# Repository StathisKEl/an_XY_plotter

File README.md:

An XY plotter that places an array of a Hall sensor and a strong magnet connected to two pieces of soft iron over specific points on a metal sheet and measures the changes in magnetic induction as the above array is moved from one point to another. From the measurements stored on an SD card, as well as the points of interest stored on the same SD card, useful conclusions can be drawn about the condition of the metal sheet.

The code inside the code_XY_plotter.ino file is under the GNU General Public v3.0 license and the hardware of the XY plotter such as the eagle pcb files and the eagle library files is under the CERN Open Hardware Version 2 - Strongly Reciprocal license. Also all the files of the 3D parts are under the Creative Commons Attribution Share Alike 4.0 International license. All the informations about the GNU General Public v3.0 license can be found in the GNU GPLv3 license.txt file, all the informations about the CERN Open Hardware Version 2 - Strongly Reciprocal license can be found in the CERN OHL S 2.0 license.txt file and all the informations about the Creative Commons Attribution Share Alike 4.0 International license can be found in the CC-BY-SA-4.0 license.txt file.

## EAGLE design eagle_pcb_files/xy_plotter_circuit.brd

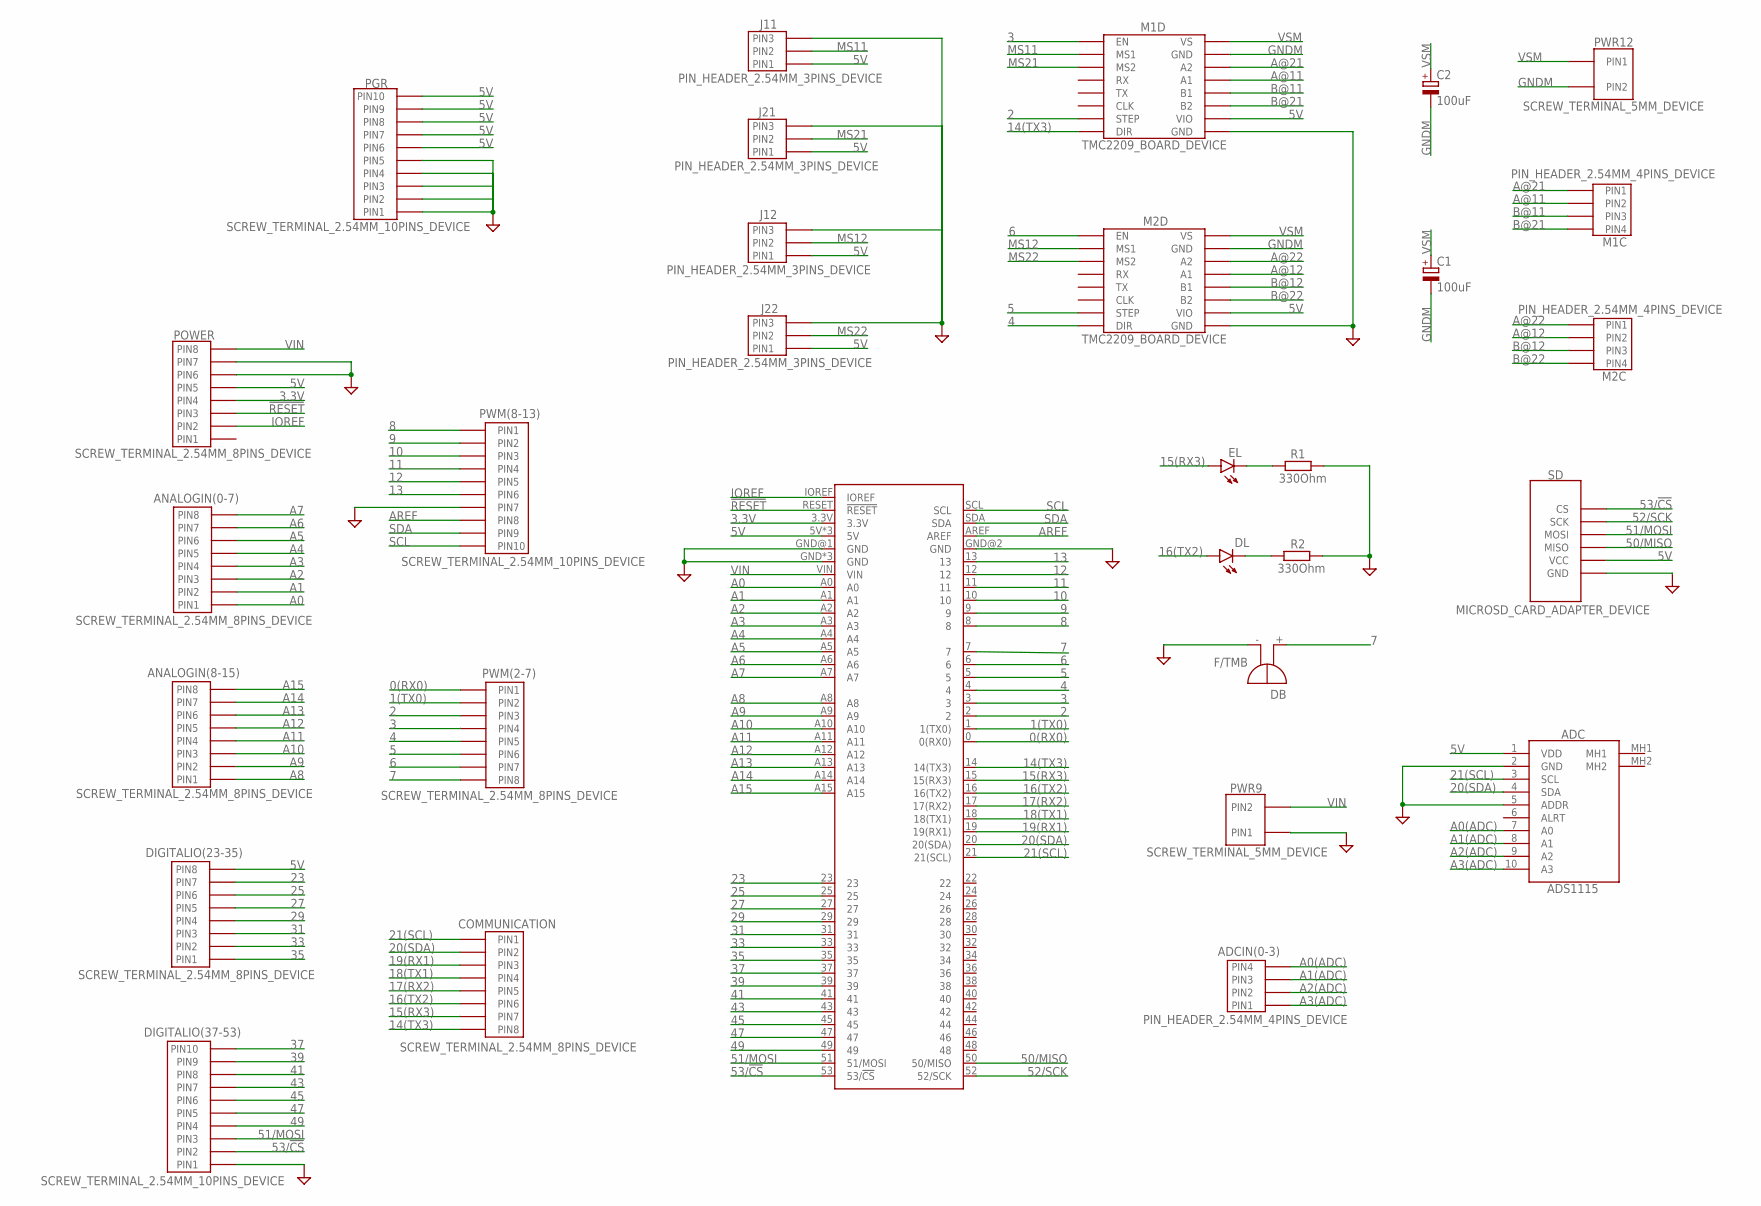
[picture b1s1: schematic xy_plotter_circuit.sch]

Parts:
ADC: ADS1115
ADCIN(0-3): PIN_HEADER_2.54MM_4PINS_DEVICE; PIN_HEADER_2.54MM_4PINS_FOOTPRINT
ANALOGIN(0-7), ANALOGIN(8-15): SCREW_TERMINAL_2.54MM_8PINS_DEVICE; SCREW_TERMINAL_2.54MM_8PINS_FOOTPRINT
ARDUINO: ARDUINO_MEGA_R3FULL; ARDUINO_MEGA_NO_SILK
C1, C2: 100uF; E2,5-7
COMMUNICATION: SCREW_TERMINAL_2.54MM_8PINS_DEVICE; SCREW_TERMINAL_2.54MM_8PINS_FOOTPRINT
DB: F/TMB
DIGITALIO(23-35): SCREW_TERMINAL_2.54MM_8PINS_DEVICE; SCREW_TERMINAL_2.54MM_8PINS_FOOTPRINT
DIGITALIO(37-53): SCREW_TERMINAL_2.54MM_10PINS_DEVICE; SCREW_TERMINAL_2.54MM_10PINS_FOOTPRINT
DL: LED3MM
EL: LED3MM
J11, J12, J21, J22: PIN_HEADER_2.54MM_3PINS_DEVICE; PIN_HEADER_2.54MM_3PINS_FOOTPRINT
M1C, M2C: PIN_HEADER_2.54MM_4PINS_DEVICE; PIN_HEADER_2.54MM_4PINS_FOOTPRINT
M1D, M2D: TMC2209_BOARD_DEVICE; TMC2209_BOARD_FOOTPRINT
PGR: SCREW_TERMINAL_2.54MM_10PINS_DEVICE; SCREW_TERMINAL_2.54MM_10PINS_FOOTPRINT
POWER: SCREW_TERMINAL_2.54MM_8PINS_DEVICE; SCREW_TERMINAL_2.54MM_8PINS_FOOTPRINT
PWM(2-7): SCREW_TERMINAL_2.54MM_8PINS_DEVICE; SCREW_TERMINAL_2.54MM_8PINS_FOOTPRINT
PWM(8-13): SCREW_TERMINAL_2.54MM_10PINS_DEVICE; SCREW_TERMINAL_2.54MM_10PINS_FOOTPRINT
PWR9, PWR12: SCREW_TERMINAL_5MM_DEVICE; SCREW_TERMINAL_5MM_FOOTPRINT
R1, R2: 330Ohm; 0207/7
SD: MICROSD_CARD_ADAPTER_DEVICE; MICROSD_CARD_ADAPTER_FOOTPRINT

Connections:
0(RX0): ARDUINO.0 (0(RX0)), PWM(2-7).PIN1
1(TX0): ARDUINO.1 (1(TX0)), PWM(2-7).PIN2
2: ARDUINO.2, M1D.STEP, PWM(2-7).PIN3
3: ARDUINO.3, M1D.EN, PWM(2-7).PIN4
3.3V: ARDUINO.3.3V, POWER.PIN4
4: ARDUINO.4, M2D.DIR, PWM(2-7).PIN5
5: ARDUINO.5, M2D.STEP, PWM(2-7).PIN6
5V: ADC.1 (VDD), ARDUINO.5V, ARDUINO.5V@1 (5V), ARDUINO.5V@2 (5V), DIGITALIO(23-35).PIN8, J11.PIN1, J12.PIN1, J21.PIN1, J22.PIN1, M1D.VIO, M2D.VIO, PGR.PIN6, PGR.PIN7, PGR.PIN8, PGR.PIN9, PGR.PIN10, POWER.PIN5, SD.VCC
6: ARDUINO.6, M2D.EN, PWM(2-7).PIN7
7: ARDUINO.7, DB.+, PWM(2-7).PIN8
8: ARDUINO.8, PWM(8-13).PIN1
9: ARDUINO.9, PWM(8-13).PIN2
10: ARDUINO.10, PWM(8-13).PIN3
11: ARDUINO.11, PWM(8-13).PIN4
12: ARDUINO.12, PWM(8-13).PIN5
13: ARDUINO.13, PWM(8-13).PIN6
14(TX3): ARDUINO.14 (14(TX3)), COMMUNICATION.PIN8, M1D.DIR
15(RX3): ARDUINO.15 (15(RX3)), COMMUNICATION.PIN7, EL.A
16(TX2): ARDUINO.16 (16(TX2)), COMMUNICATION.PIN6, DL.A
17(RX2): ARDUINO.17 (17(RX2)), COMMUNICATION.PIN5
18(TX1): ARDUINO.18 (18(TX1)), COMMUNICATION.PIN4
19(RX1): ARDUINO.19 (19(RX1)), COMMUNICATION.PIN3
20(SDA): ADC.4 (SDA), ARDUINO.20 (20(SDA)), COMMUNICATION.PIN2
21(SCL): ADC.3 (SCL), ARDUINO.21 (21(SCL)), COMMUNICATION.PIN1
23: ARDUINO.23, DIGITALIO(23-35).PIN7
25: ARDUINO.25, DIGITALIO(23-35).PIN6
27: ARDUINO.27, DIGITALIO(23-35).PIN5
29: ARDUINO.29, DIGITALIO(23-35).PIN4
31: ARDUINO.31, DIGITALIO(23-35).PIN3
33: ARDUINO.33, DIGITALIO(23-35).PIN2
35: ARDUINO.35, DIGITALIO(23-35).PIN1
37: ARDUINO.37, DIGITALIO(37-53).PIN10
39: ARDUINO.39, DIGITALIO(37-53).PIN9
41: ARDUINO.41, DIGITALIO(37-53).PIN8
43: ARDUINO.43, DIGITALIO(37-53).PIN7
45: ARDUINO.45, DIGITALIO(37-53).PIN6
47: ARDUINO.47, DIGITALIO(37-53).PIN5
49: ARDUINO.49, DIGITALIO(37-53).PIN4
50/MISO: ARDUINO.50 (50/MISO), SD.MISO
51/MOSI: ARDUINO.51 (51/MOSI), DIGITALIO(37-53).PIN3, SD.MOSI
52/SCK: ARDUINO.52 (52/SCK), SD.SCK
53/!CS: ARDUINO.53 (53/!CS), DIGITALIO(37-53).PIN2, SD.CS
!RESET: ARDUINO.RESET (!RESET), POWER.PIN3
A0: ANALOGIN(0-7).PIN1, ARDUINO.A0
A0(ADC): ADC.7 (A0), ADCIN(0-3).PIN4
A1: ANALOGIN(0-7).PIN2, ARDUINO.A1
A1(ADC): ADC.8 (A1), ADCIN(0-3).PIN3
A2: ANALOGIN(0-7).PIN3, ARDUINO.A2
A2(ADC): ADC.9 (A2), ADCIN(0-3).PIN2
A3: ANALOGIN(0-7).PIN4, ARDUINO.A3
A3(ADC): ADC.10 (A3), ADCIN(0-3).PIN1
A4: ANALOGIN(0-7).PIN5, ARDUINO.A4
A5: ANALOGIN(0-7).PIN6, ARDUINO.A5
A6: ANALOGIN(0-7).PIN7, ARDUINO.A6
A7: ANALOGIN(0-7).PIN8, ARDUINO.A7
A8: ANALOGIN(8-15).PIN1, ARDUINO.A8
A9: ANALOGIN(8-15).PIN2, ARDUINO.A9
A10: ANALOGIN(8-15).PIN3, ARDUINO.A10
A11: ANALOGIN(8-15).PIN4, ARDUINO.A11
A12: ANALOGIN(8-15).PIN5, ARDUINO.A12
A13: ANALOGIN(8-15).PIN6, ARDUINO.A13
A14: ANALOGIN(8-15).PIN7, ARDUINO.A14
A15: ANALOGIN(8-15).PIN8, ARDUINO.A15
A@11: M1C.PIN2, M1D.A1
A@12: M2C.PIN2, M2D.A1
A@21: M1C.PIN1, M1D.A2
A@22: M2C.PIN1, M2D.A2
AREF: ARDUINO.AREF, PWM(8-13).PIN8
B@11: M1C.PIN3, M1D.B1
B@12: M2C.PIN3, M2D.B1
B@21: M1C.PIN4, M1D.B2
B@22: M2C.PIN4, M2D.B2
GND: ADC.2 (GND), ADC.5 (ADDR), ARDUINO.GND, ARDUINO.GND@1 (GND), ARDUINO.GND@2 (GND), ARDUINO.GND@3 (GND), ARDUINO.GND@4 (GND), DB.-, DIGITALIO(37-53).PIN1, J11.PIN3, J12.PIN3, J21.PIN3, J22.PIN3, M1D.GND@2 (GND), M2D.GND@2 (GND), PGR.PIN1, PGR.PIN2, PGR.PIN3, PGR.PIN4, PGR.PIN5, POWER.PIN6, POWER.PIN7, PWM(8-13).PIN7, PWR9.PIN1, R1.2, R2.2, SD.GND
GNDM: C1.-, C2.-, M1D.GND@1 (GND), M2D.GND@1 (GND), PWR12.PIN2
IOREF: ARDUINO.IOREF, POWER.PIN2
MS11: J11.PIN2, M1D.MS1
MS12: J12.PIN2, M2D.MS1
MS21: J21.PIN2, M1D.MS2
MS22: J22.PIN2, M2D.MS2
unnamed: EL.K (C), R1.1
unnamed: DL.K (C), R2.1
SCL: ARDUINO.SCL, PWM(8-13).PIN10
SDA: ARDUINO.SDA, PWM(8-13).PIN9
VIN: ARDUINO.VIN, POWER.PIN8, PWR9.PIN2
VSM: C1.+, C2.+, M1D.VS, M2D.VS, PWR12.PIN1

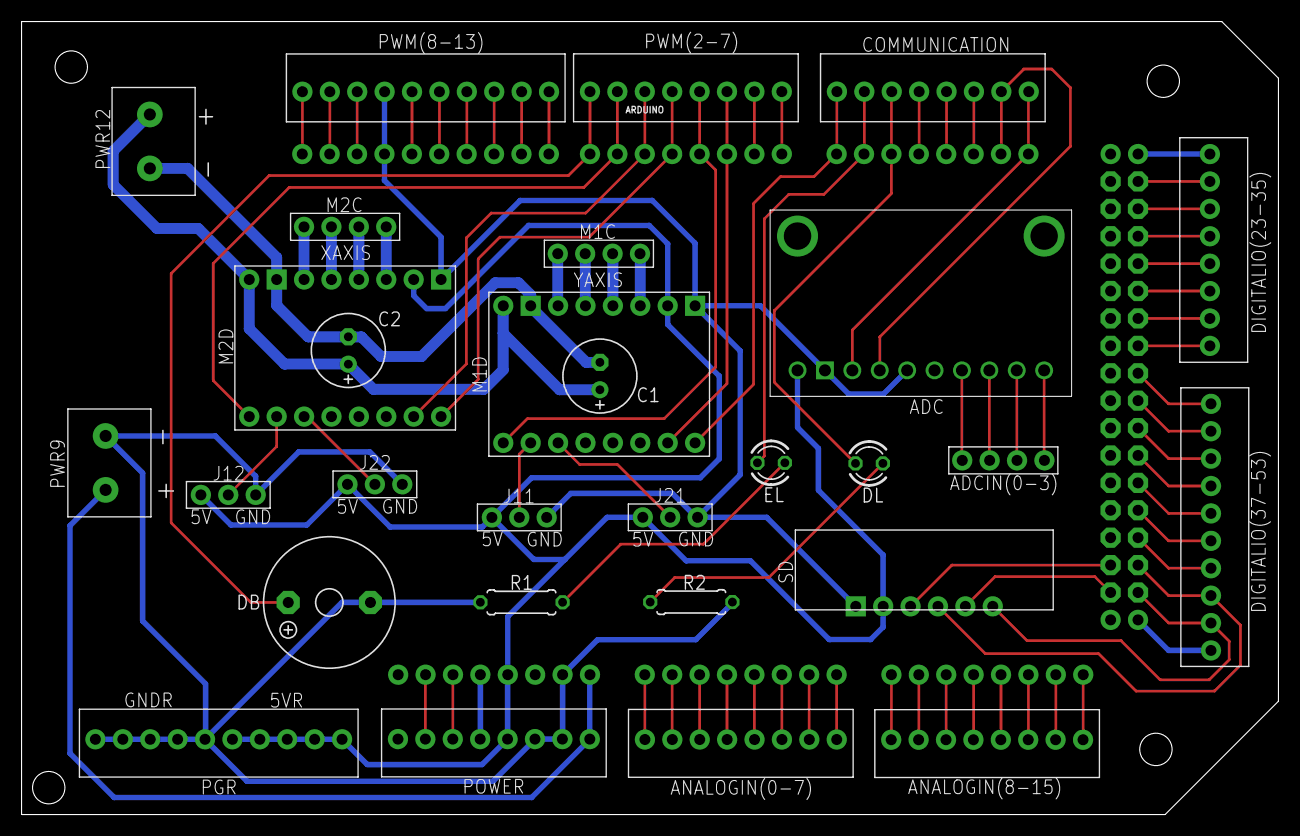
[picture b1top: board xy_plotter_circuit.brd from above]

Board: 2 copper layers, 116.5 x 73.5 mm, 30 parts (0 on the bottom side), 85 nets.

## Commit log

2025-08-20 The main files of the project has been uploaded

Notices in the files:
parts and their libraries:
SparkFun-Boards: Licensing: Creative Commons ShareAlike 4.0 International - https://creativecommons.org/licenses/by-sa/4.0
